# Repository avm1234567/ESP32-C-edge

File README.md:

<h1 align="center">ESP32-C-edge</h1>

This project is a custom-designed ESP32-S3 development board created by me, featuring a USB Type-C edge connector directly integrated into the PCB. The board is intended to be compact, easy to manufacture, and convenient for prototyping without requiring a separate USB connector footprint.

---

## Overview

- MCU: **ESP32-S3**
- USB Interface: **USB Type-C via PCB edge connector**
- Purpose:
  - Minimal and compact ESP32-S3 dev board  
  - Direct USB connection without soldered connector  
  - Useful for experiments, prototypes, and small form-factor designs  
  - Learning project for PCB edge connectors and USB-C implementation  

---

## Features

- USB Type-C edge connector
- On-board ESP32-S3
- There are 3 USB Type-C in this design
    - Two on the right side are connected to a USB-TTL (CP2102).
    - One on the left is connected to D+ and D- pins of ESP32-S3.

---

## Results
|            3D-Viewer           |            Actual            |
| ------------------------------ | ---------------------------- |
|         |  |

---

## Tools Used

- PCB Design Software: KiCad
- MCU: ESP32-S3
- Fabrication: [JLCPCB](https://jlcpcb.com/)
- PCB-Thickness: 0.6 mm

---

## Future Work

- Improve the silkscreen of PCB.
- Change the corners of PCB.
- Try with 0.8 mm PCB thickness.

---

## Acknowledgement

Special thanks to [AnasMalas](https://github.com/AnasMalas) for publishing the USB Type-C edge connector design which made this project possible and [SRA-VJTI](https://github.com/SRA-VJTI) for providing the components, technical guidance, and hands-on support during the PCB design and development process.

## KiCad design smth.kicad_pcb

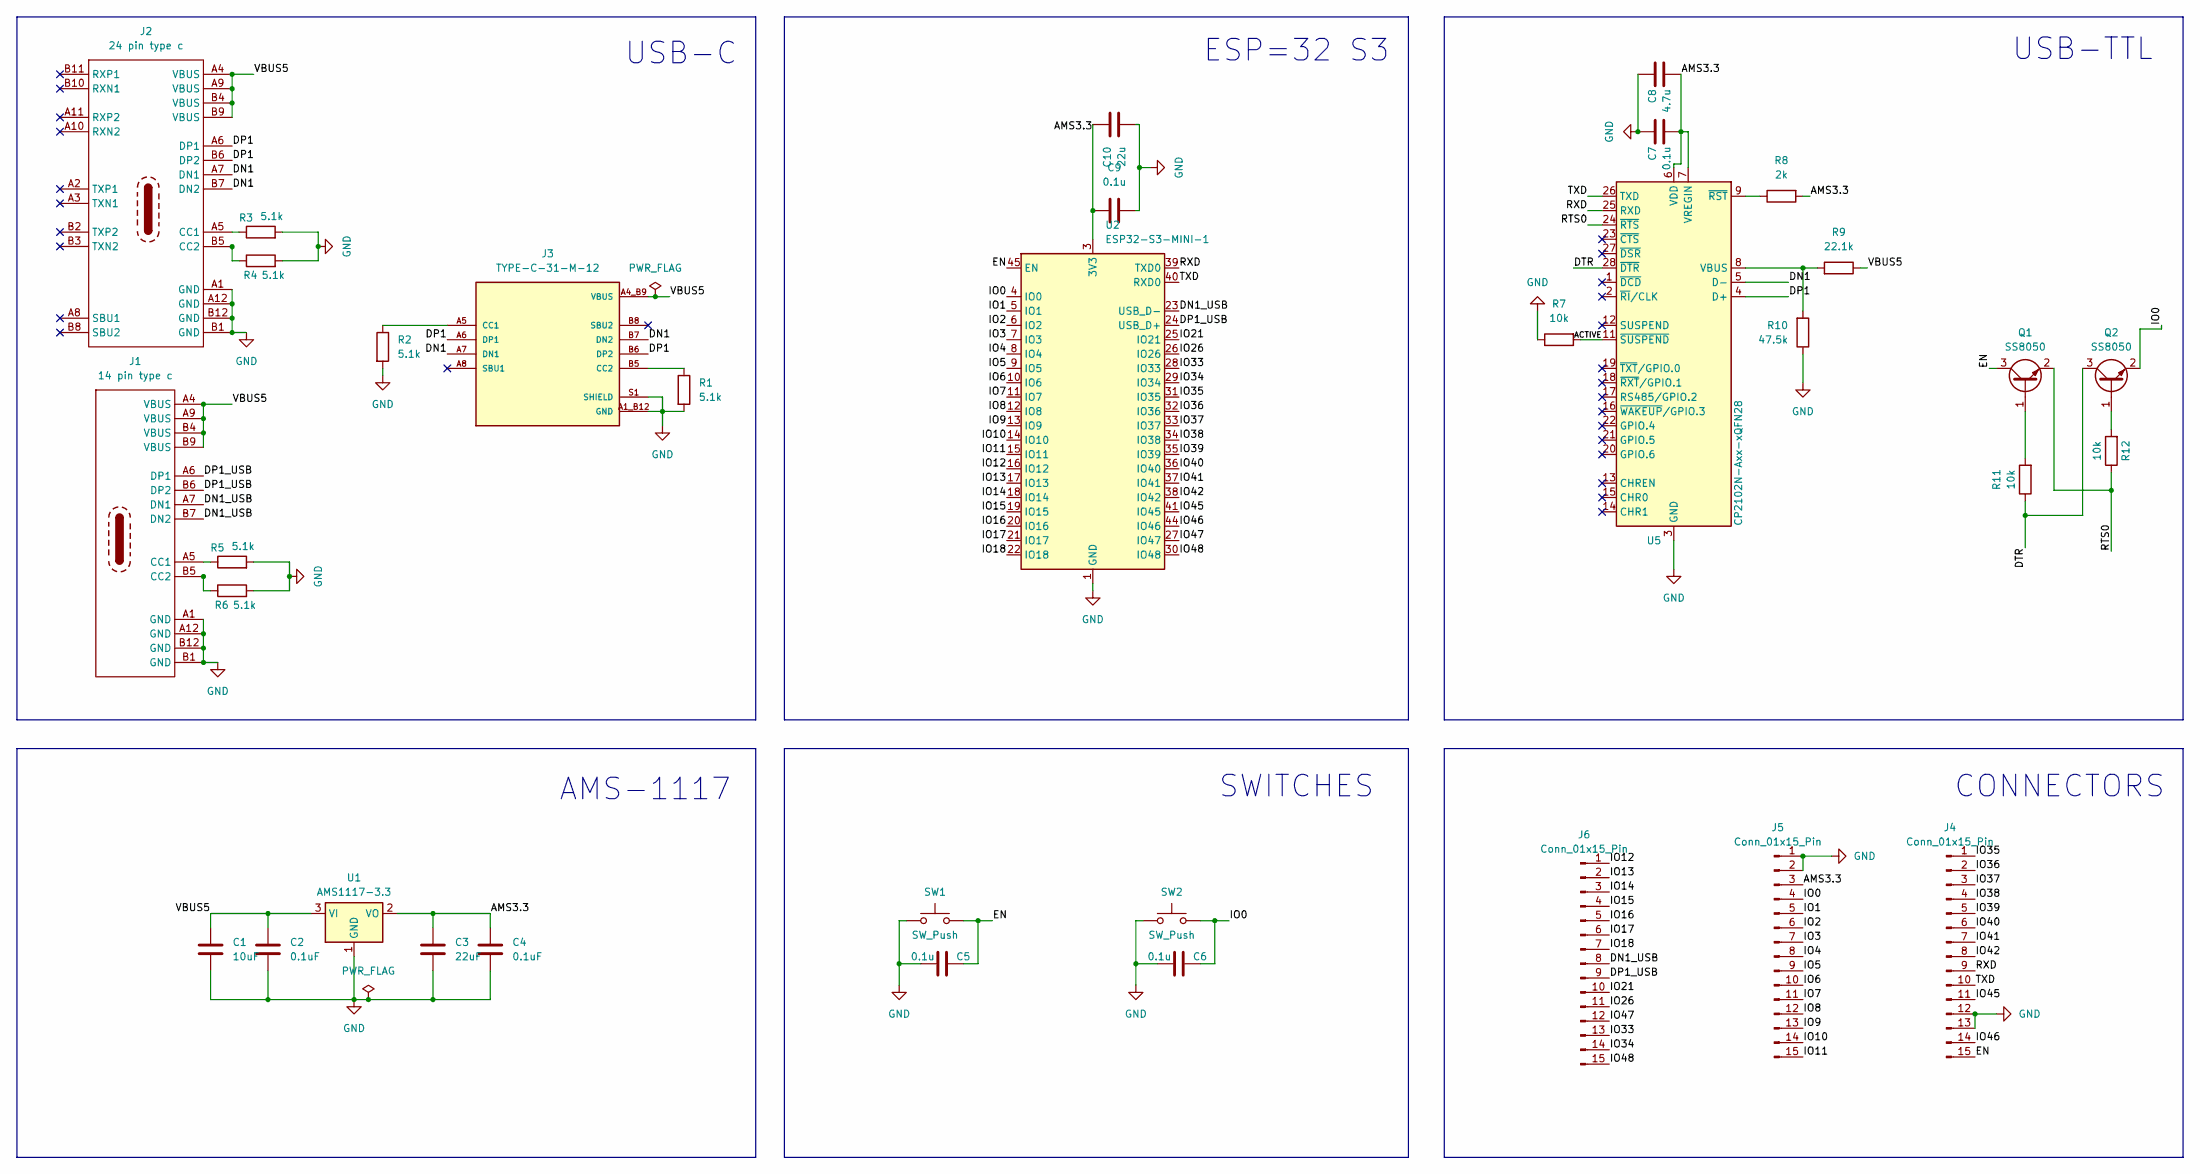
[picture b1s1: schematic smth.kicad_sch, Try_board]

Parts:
C1: 10uF; C_0805_2012Metric_Pad1.18x1.45mm_HandSolder
C2, C4: 0.1uF; C_0805_2012Metric_Pad1.18x1.45mm_HandSolder
C3: 22uF; C_0805_2012Metric_Pad1.18x1.45mm_HandSolder
C5, C6, C7, C9: 0.1u; C_0805_2012Metric_Pad1.18x1.45mm_HandSolder
C8: 4.7u; C_0805_2012Metric_Pad1.18x1.45mm_HandSolder
C10: 22u; C_0805_2012Metric_Pad1.18x1.45mm_HandSolder
J1: 14 pin type c; PCBTypeC_14P
J2: 24 pin type c; PCBTypeC_14P
J3: TYPE-C-31-M-12; HRO_TYPE-C-31-M-12; PARTREV 2020.12.08
J4, J5, J6: Conn_01x15_Pin; PinHeader_1x14_P2.54mm_Vertical
Q1, Q2: SS8050; SOT-23
R1, R2, R3, R4, R5, R6: 5.1k; R_0805_2012Metric_Pad1.20x1.40mm_HandSolder
R7, R11, R12: 10k; R_0805_2012Metric_Pad1.20x1.40mm_HandSolder
R8: 2k; R_0805_2012Metric_Pad1.20x1.40mm_HandSolder
R9: 22.1k; R_0805_2012Metric_Pad1.20x1.40mm_HandSolder
R10: 47.5k; R_0805_2012Metric_Pad1.20x1.40mm_HandSolder
SW1, SW2: SW_Push; SW_Push_SPST_NO_Alps_SKRK
U1: AMS1117-3.3; SOT-223-3_TabPin2
U2: ESP32-S3-MINI-1; ESP32-S2-MINI-1
U5: CP2102N-Axx-xQFN28; QFN-28-1EP_5x5mm_P0.5mm_EP3.35x3.35mm

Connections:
/ACTIVE: R7.2, U5.11 (~SUSPEND)
/AMS3.3: C3.1, C4.1, C7.2, C8.2, C9.1, C10.1, J5.3, R8.2, U1.2 (VO), U2.3 (3V3), U5.6 (VDD), U5.7 (VREGIN)
/DN1: J2.A7 (DN1), J2.B7 (DN2), J3.A7 (DN1), J3.B7 (DN2), U5.5 (D-)
/DN1_USB: J1.A7 (DN1), J1.B7 (DN2), J6.8, U2.23 (USB_D-)
/DP1: J2.A6 (DP1), J2.B6 (DP2), J3.A6 (DP1), J3.B6 (DP2), U5.4 (D+)
/DP1_USB: J1.A6 (DP1), J1.B6 (DP2), J6.9, U2.24 (USB_D+)
/DTR: Q2.3 (C), R11.1, U5.28 (~DTR)
/EN: C5.1, J4.15, Q1.3 (C), SW1.2, U2.45 (EN)
/IO0: C6.1, J5.4, Q2.2 (E), SW2.2, U2.4 (IO0)
/IO1: J5.5, U2.5 (IO1)
/IO2: J5.6, U2.6 (IO2)
/IO3: J5.7, U2.7 (IO3)
/IO4: J5.8, U2.8 (IO4)
/IO5: J5.9, U2.9 (IO5)
/IO6: J5.10, U2.10 (IO6)
/IO7: J5.11, U2.11 (IO7)
/IO8: J5.12, U2.12 (IO8)
/IO9: J5.13, U2.13 (IO9)
/IO10: J5.14, U2.14 (IO10)
/IO11: J5.15, U2.15 (IO11)
/IO12: J6.1, U2.16 (IO12)
/IO13: J6.2, U2.17 (IO13)
/IO14: J6.3, U2.18 (IO14)
/IO15: J6.4, U2.19 (IO15)
/IO16: J6.5, U2.20 (IO16)
/IO17: J6.6, U2.21 (IO17)
/IO18: J6.7, U2.22 (IO18)
/IO21: J6.10, U2.25 (IO21)
/IO26: J6.11, U2.26 (IO26)
/IO33: J6.13, U2.28 (IO33)
/IO34: J6.14, U2.29 (IO34)
/IO35: J4.1, U2.31 (IO35)
/IO36: J4.2, U2.32 (IO36)
/IO37: J4.3, U2.33 (IO37)
/IO38: J4.4, U2.34 (IO38)
/IO39: J4.5, U2.35 (IO39)
/IO40: J4.6, U2.36 (IO40)
/IO41: J4.7, U2.37 (IO41)
/IO42: J4.8, U2.38 (IO42)
/IO45: J4.11, U2.41 (IO45)
/IO46: J4.14, U2.44 (IO46)
/IO47: J6.12, U2.27 (IO47)
/IO48: J6.15, U2.30 (IO48)
/RTS0: Q1.2 (E), R12.1, U5.24 (~RTS)
/RXD: J4.9, U2.39 (TXD0), U5.25 (RXD)
/TXD: J4.10, U2.40 (RXD0), U5.26 (TXD)
GND: C1.2, C2.2, C3.2, C4.2, C5.2, C6.2, C7.1, C8.1, C9.2, C10.2, J1.A1 (GND), J1.A12 (GND), J1.B1 (GND), J1.B12 (GND), J2.A1 (GND), J2.A12 (GND), J2.B1 (GND), J2.B12 (GND), J3.A1_B12 (GND), J3.B1_A12 (GND), J3.S1 (SHIELD), J3.S2 (SHIELD), J3.S3 (SHIELD), J3.S4 (SHIELD), J4.12, J4.13, J5.1, J5.2, R1.2, R2.2, R3.2, R4.2, R5.2, R6.2, R7.1, R10.1, SW1.1, SW2.1, U1.1 (GND), U2.1 (GND), U2.2 (GND), U2.42 (GND), U2.43 (GND), U2.46 (GND), U2.47 (GND), U2.48 (GND), U2.49 (GND), U2.50 (GND), U2.51 (GND), U2.52 (GND), U2.53 (GND), U2.54 (GND), U2.55 (GND), U2.56 (GND), U2.57 (GND), U2.58 (GND), U2.59 (GND), U2.60 (GND), U2.61 (GND), U2.62 (GND), U2.63 (GND), U2.64 (GND), U2.65 (GND), U5.3 (GND), U5.29 (GND)
unnamed: J1.A5 (CC1), R5.1
unnamed: J1.B5 (CC2), R6.1
unnamed: J2.A5 (CC1), R3.1
unnamed: J2.B5 (CC2), R4.1
unnamed: J3.A5 (CC1), R2.1
unnamed: J3.B5 (CC2), R1.1
unnamed: Q1.1 (B), R11.2
unnamed: Q2.1 (B), R12.2
unnamed: R9.2, R10.2, U5.8 (VBUS)
unnamed: R8.1, U5.9 (~RST)
VBUS: C1.1, C2.1, J1.A4 (VBUS), J1.A9 (VBUS), J1.B4 (VBUS), J1.B9 (VBUS), J2.A4 (VBUS), J2.A9 (VBUS), J2.B4 (VBUS), J2.B9 (VBUS), J3.A4_B9 (VBUS), J3.B4_A9 (VBUS), R9.1, U1.3 (VI)

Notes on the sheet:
SWITCHES
ESP=32 S3
CONNECTORS
USB-C
AMS-1117
USB-TTL

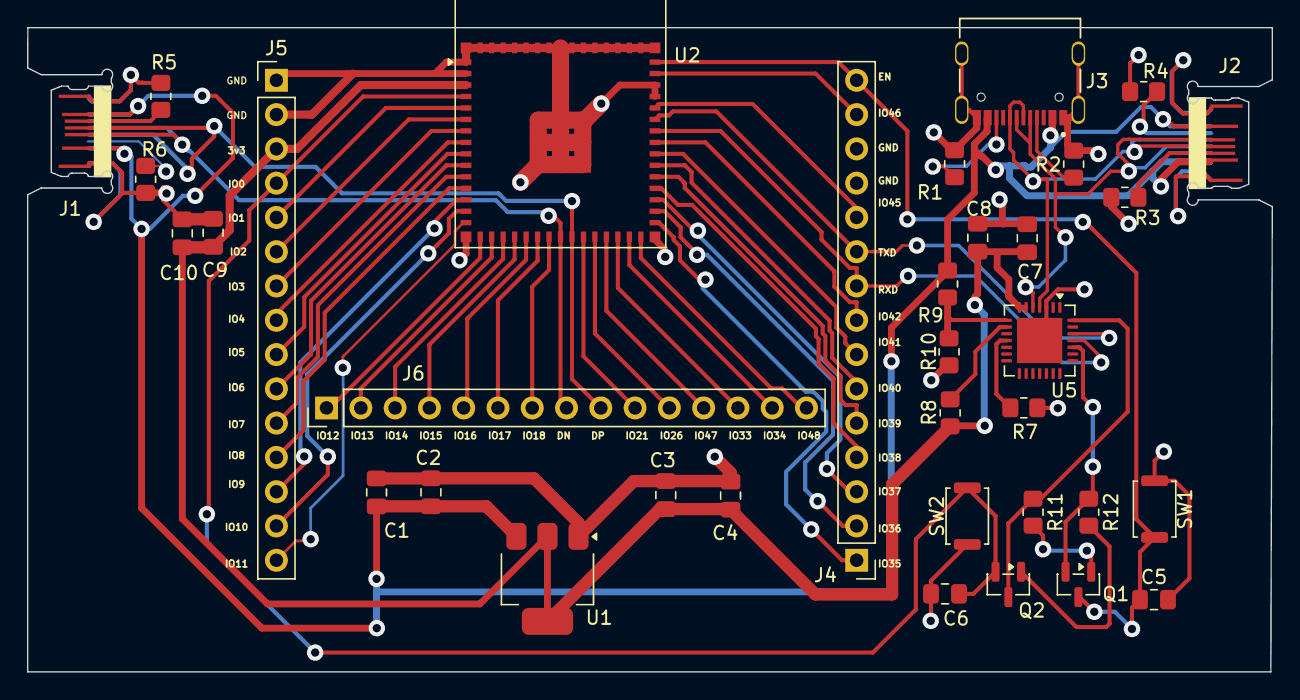
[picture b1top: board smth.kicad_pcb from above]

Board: 2 copper layers, 92.2 x 47.7 mm, 35 parts (0 on the bottom side), 58 nets.

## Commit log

2026-01-28 Schematic and PCB file
2026-01-28 Assets added
2026-01-28 Readme Modified
